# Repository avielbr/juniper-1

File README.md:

### Relevant datasheets:
- [ESP32-S2-WROOM](https://www.4project.co.il/documents/doc_664512_968259.pdf)
- [TMC6200-TA](https://www.mouser.co.il/datasheet/2/256/TMC6200_datasheet_Rev1_05-2529504.pdf) -- I also grabbed what I could from the picture in [this](https://community.simplefoc.com/t/esp32-s3-tmc6200-test-board/2418) thread discussing a board with the same MCU + gate driver.
- [NTMFS5C645NL](https://www.mouser.co.il/datasheet/2/308/NTMFS5C645NL_D-1814050.pdf) MOSFET
- [LDL1117S33R](https://www.mouser.co.il/datasheet/2/389/dm00366442-1799212.pdf) voltage regulator
- [TXU0104PWR](https://www.ti.com/lit/ds/symlink/txu0104.pdf?HQS=dis-mous-null-mousermode-dsf-pf-null-wwe&ts=1665879126738&ref_url=https%253A%252F%252Fwww.mouser.com%252F) level shifter

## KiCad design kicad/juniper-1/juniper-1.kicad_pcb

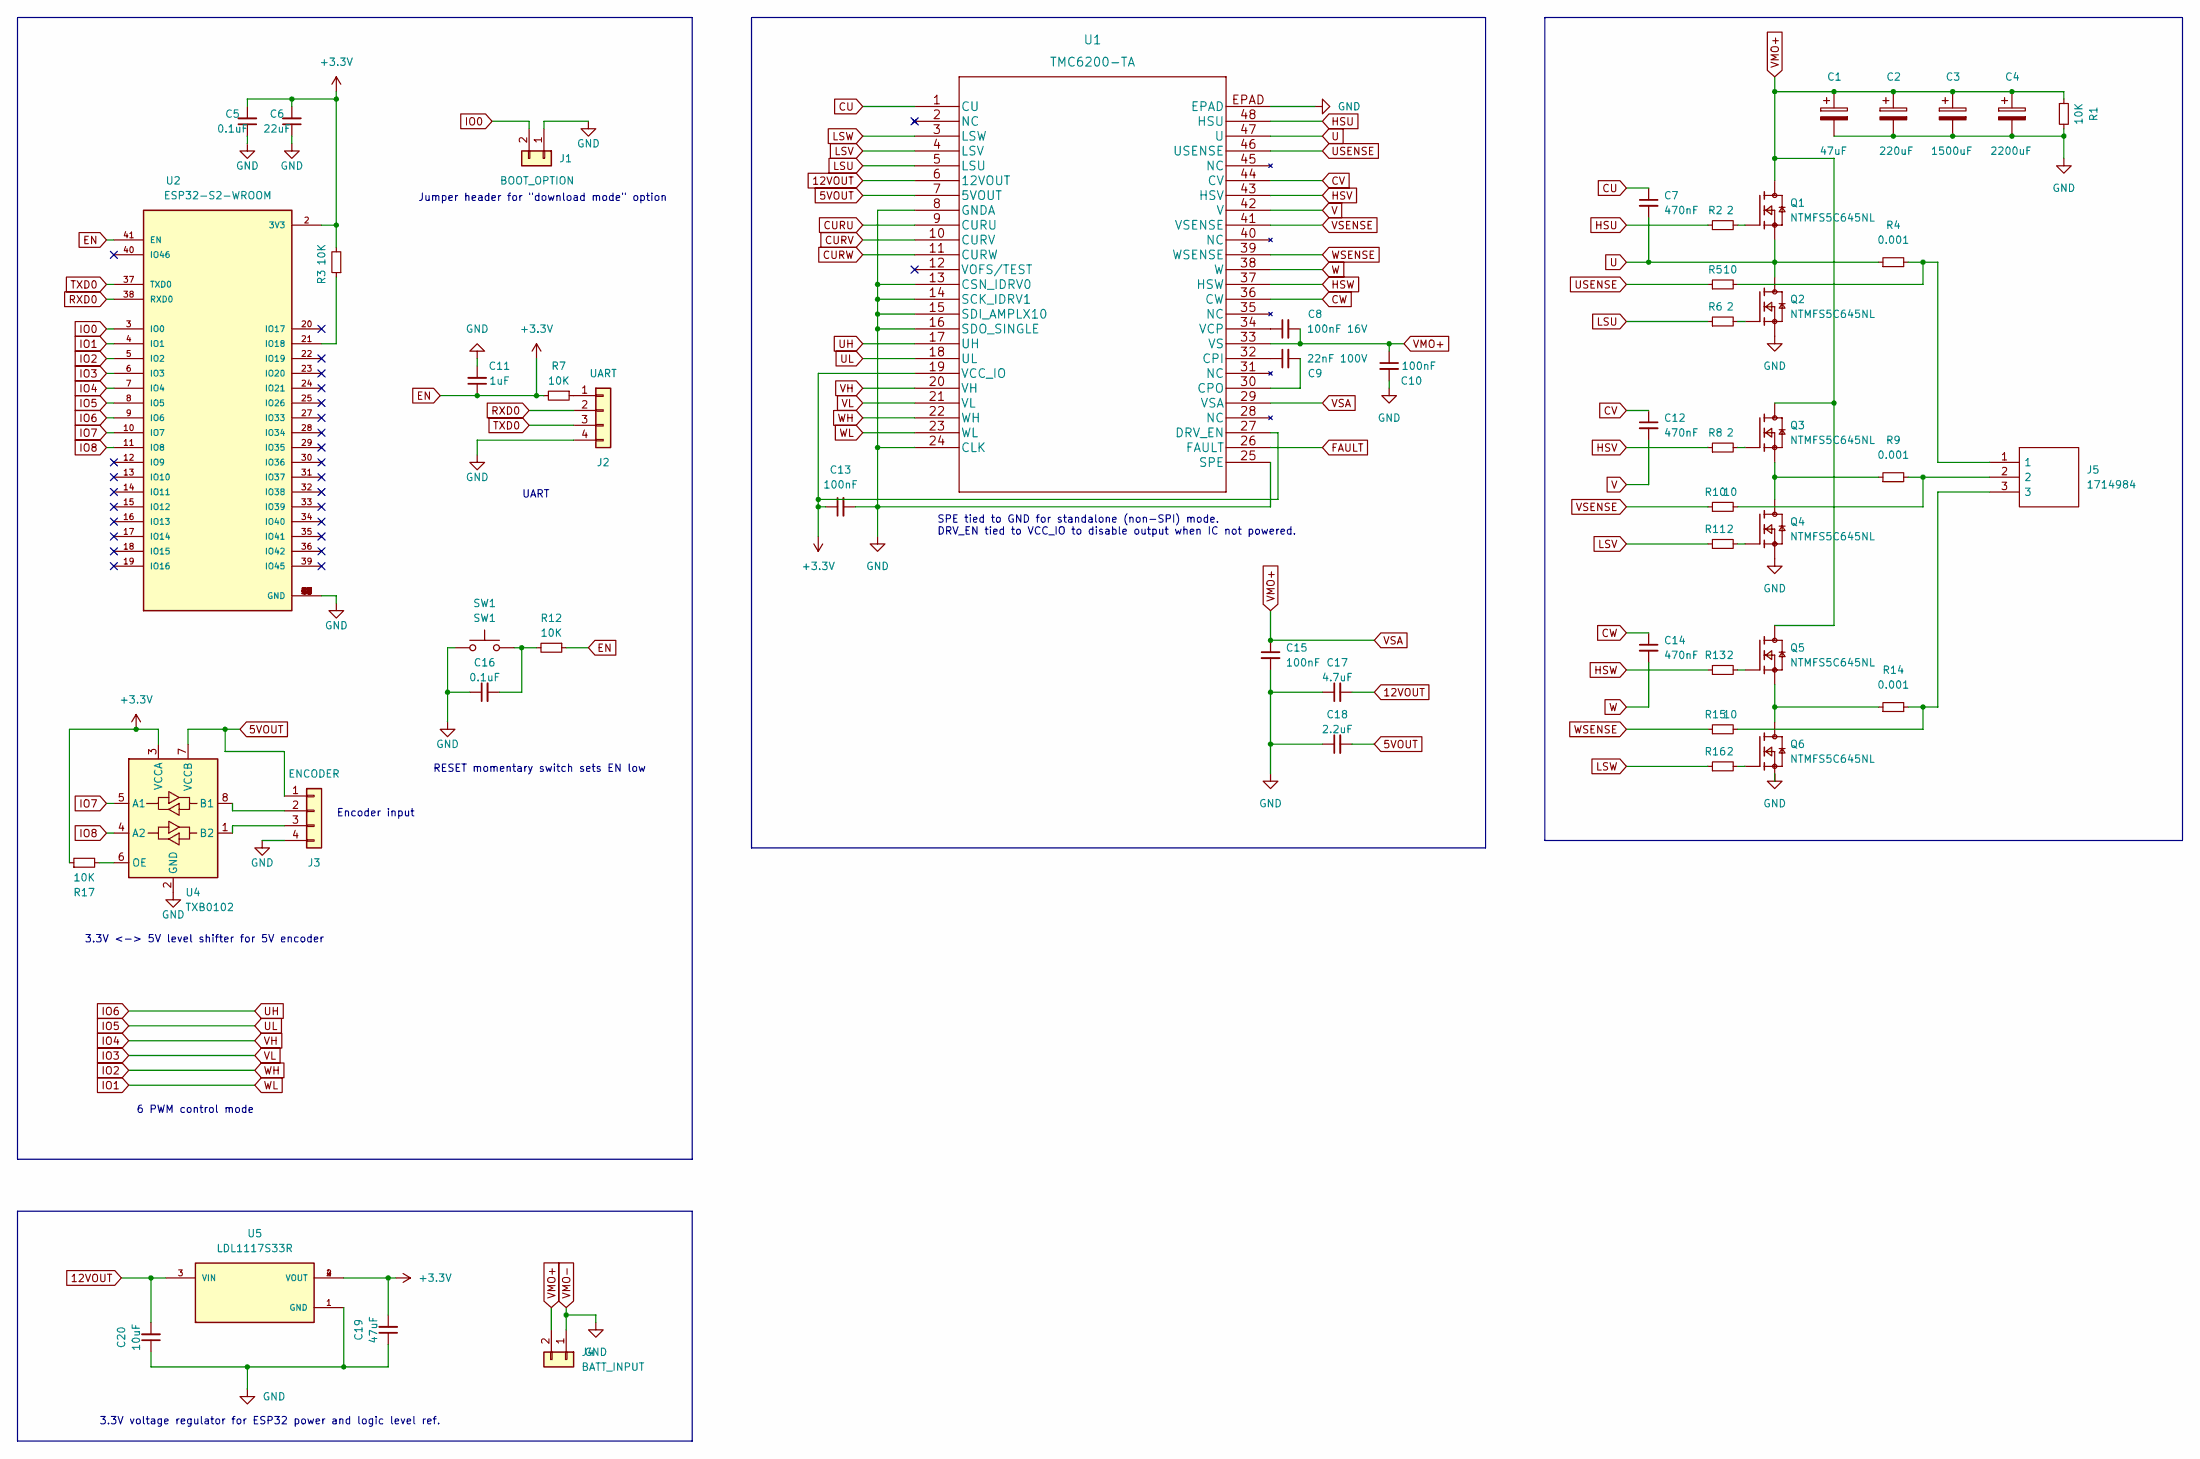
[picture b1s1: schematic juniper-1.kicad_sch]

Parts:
C1: 47uF; CP_Elec_10x10.5
C2: 220uF; CP_Elec_10x10.5
C3: 1500uF; CP_Elec_10x10.5
C4: 2200uF; CP_Elec_10x10.5
C5, C16: 0.1uF; C_0402_1005Metric
C6: 22uF; C_0402_1005Metric
C7, C12, C14: 470nF; C_0402_1005Metric
C8: 100nF 16V; C_0402_1005Metric
C9: 22nF 100V; C_0402_1005Metric
C10, C13, C15: 100nF; C_0402_1005Metric
C11: 1uF; C_0402_1005Metric
C17: 4.7uF; C_0402_1005Metric
C18: 2.2uF; C_0402_1005Metric
C19: 47uF; CP_Elec_6.3x7.7
C20: 10uF; CP_Elec_6.3x7.7
J1: BOOT_OPTION; PinHeader_1x02_P2.54mm_Vertical
J2: UART; PinHeader_1x04_P2.54mm_Vertical
J3: ENCODER; PinSocket_1x04_P2.54mm_Vertical
J4: BATT_INPUT; AMASS_XT60-F_1x02_P7.20mm_Vertical
J5: 1714984; Manufacturer_Part_Number 1714984; Mouser Part Number 651-1714984
Q1, Q2, Q3, Q4, Q5, Q6: NTMFS5C645NL; TRANS_NTMFS5C628NLT1G; PARTREV 1
R1, R3, R7, R12, R17: 10K; R_0603_1608Metric_Pad0.98x0.95mm_HandSolder
R2, R6, R8, R11, R13, R16: 2; R_0603_1608Metric_Pad0.98x0.95mm_HandSolder
R4, R9, R14: 0.001; R_0603_1608Metric_Pad0.98x0.95mm_HandSolder
R5, R10, R15: 10; R_0603_1608Metric_Pad0.98x0.95mm_HandSolder
SW1: SW1; SW_Push_1P1T_NO_CK_PTS125Sx43PSMTR
U1: TMC6200-TA
U2: ESP32-S2-WROOM; XCVR_ESP32-S2-WROOM
U4: TXB0102; TSSOP-8_3x3mm_P0.65mm
U5: LDL1117S33R; SOT230P700X180-4N; PARTREV 7

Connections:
5VOUT: C18.2, J3.1, U1.7 (5VOUT), U4.7 (VCCB)
12VOUT: C17.2, C20.2, U1.6 (12VOUT), U5.3 (VIN)
CU: C7.1, U1.1 (CU)
CURU: U1.9 (CURU)
CURV: U1.10 (CURV)
CURW: U1.11 (CURW)
CV: C12.1, U1.44 (CV)
CW: C14.1, U1.36 (CW)
EN: C5.2, C6.2, C11.1, C13.1, C19.2, R3.2, R7.2, R12.1, R17.1, U1.19 (VCC_IO), U1.27 (DRV_EN), U2.2 (3V3), U2.41 (EN), U4.3 (VCCA), U5.2 (VOUT), U5.4 (VOUT)
FAULT: U1.26 (FAULT)
HSU: R2.1, U1.48 (HSU)
HSV: R8.1, U1.43 (HSV)
HSW: R13.1, U1.37 (HSW)
IO0: J1.2, U2.3 (IO0)
IO1: U1.23 (WL), U2.4 (IO1)
IO2: U1.22 (WH), U2.5 (IO2)
IO3: U1.21 (VL), U2.6 (IO3)
IO4: U1.20 (VH), U2.7 (IO4)
IO5: U1.18 (UL), U2.8 (IO5)
IO6: U1.17 (UH), U2.9 (IO6)
IO7: U2.10 (IO7), U4.5 (A1)
IO8: U2.11 (IO8), U4.4 (A2)
LSU: R6.1, U1.5 (LSU)
LSV: R11.1, U1.4 (LSV)
LSW: R16.1, U1.3 (LSW)
unnamed: C8.1, U1.34 (VCP)
unnamed: C9.1, U1.32 (CPI)
unnamed: C9.2, U1.30 (CPO)
unnamed: C16.2, R12.2, SW1.2
unnamed: J2.1, R7.1
unnamed: J3.2, U4.8 (B1)
unnamed: J3.3, U4.1 (B2)
unnamed: Q1.4, R2.2
unnamed: Q2.4, R6.2
unnamed: Q3.1, Q3.2, Q3.3, Q4.5, R9.1
unnamed: Q3.4, R8.2
unnamed: Q4.4, R11.2
unnamed: Q5.1, Q5.2, Q5.3, Q6.5, R14.1
unnamed: Q5.4, R13.2
unnamed: Q6.4, R16.2
unnamed: J5.1, R4.2, R5.2
unnamed: J5.2, R9.2, R10.2
unnamed: J5.3, R14.2, R15.2
unnamed: R3.1, U2.21 (IO18)
unnamed: R17.2, U4.6 (OE)
RXD0: J2.2, U2.38 (RXD0)
TXD0: J2.3, U2.37 (TXD0)
U: C7.2, Q1.1, Q1.2, Q1.3, Q2.5, R4.1, U1.47 (U)
USENSE: R5.1, U1.46 (USENSE)
V: C12.2, U1.42 (V)
VMO+: C1.1, C2.1, C3.1, C4.1, C8.2, C10.1, C15.1, J4.2, Q1.5, Q3.5, Q5.5, R1.1, U1.29 (VSA), U1.33 (VS)
VMO-: C1.2, C2.2, C3.2, C4.2, C5.1, C6.1, C10.2, C11.2, C13.2, C15.2, C16.1, C17.1, C18.1, C19.1, C20.1, J1.1, J2.4, J3.4, J4.1, Q2.1, Q2.2, Q2.3, Q4.1, Q4.2, Q4.3, Q6.1, Q6.2, Q6.3, R1.2, SW1.1, U1.8 (GNDA), U1.13 (CSN_IDRV0), U1.14 (SCK_IDRV1), U1.15 (SDI_AMPLX10), U1.16 (SDO_SINGLE), U1.24 (CLK), U1.25 (SPE), U1.EPAD, U2.1 (GND), U2.26 (GND), U2.42 (GND), U2.43 (GND), U2.44 (GND), U2.45 (GND), U2.46 (GND), U2.47 (GND), U2.48 (GND), U2.49 (GND), U2.50 (GND), U2.51 (GND), U4.2 (GND), U5.1 (GND)
VSENSE: R10.1, U1.41 (VSENSE)
W: C14.2, U1.38 (W)
WSENSE: R15.1, U1.39 (WSENSE)

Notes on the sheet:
UART
6 PWM control mode
3.3V voltage regulator for ESP32 power and logic level ref.
Jumper header for "download mode" option
RESET momentary switch sets EN low
3.3V <-> 5V level shifter for 5V encoder
SPE tied to GND for standalone (non-SPI) mode. DRV_EN tied to VCC_IO to disable output when IC not powered.
Encoder input

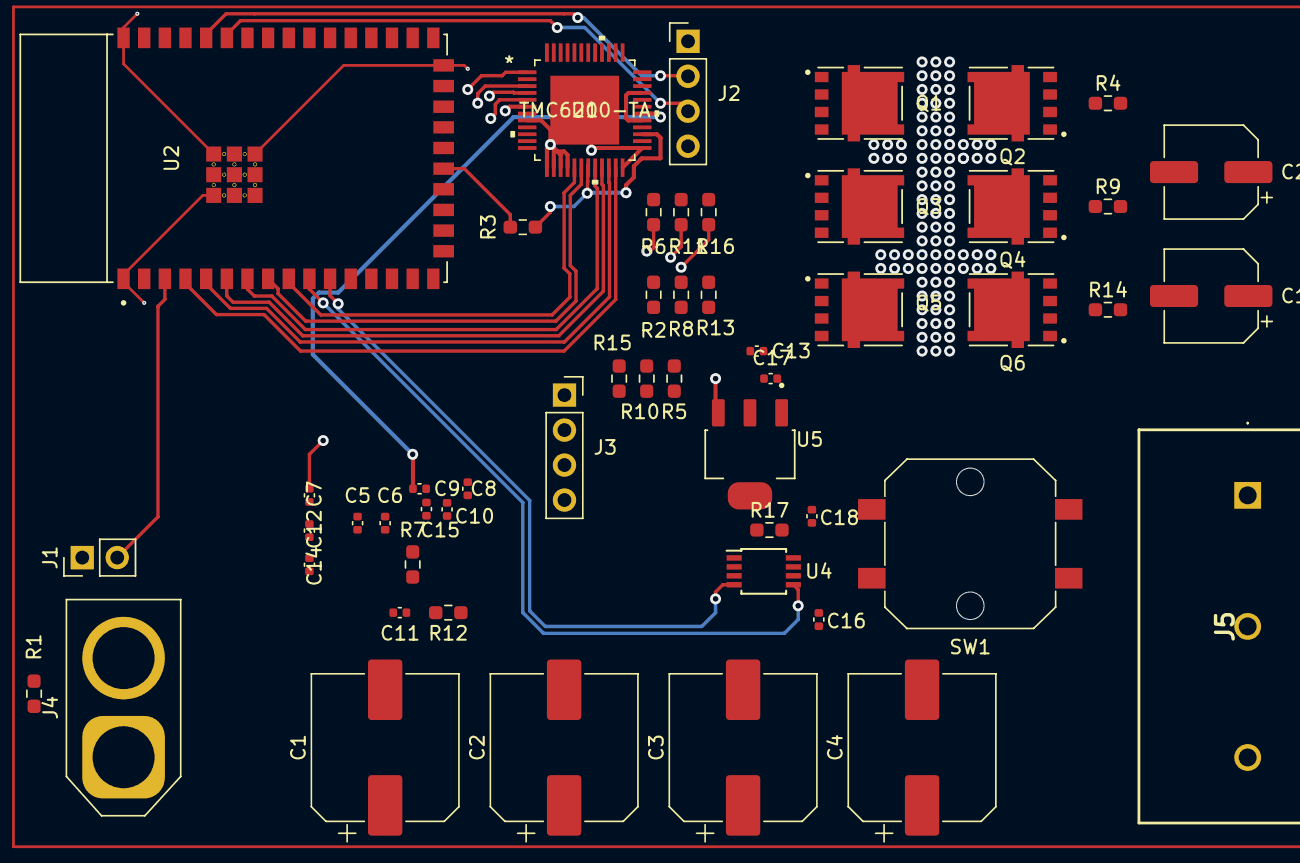
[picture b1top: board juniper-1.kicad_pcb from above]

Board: 4 copper layers, 53 parts (0 on the bottom side), 51 nets.

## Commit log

2022-10-15 Everything before assigning ESP32 pins
2022-10-15 added power supply for ESP32, haven't yet finished assigning esp32 pins
2022-10-15 fixed esp32 symbol, nearly finished assigning pins for MCU
2022-10-16 Fixed voltage regulator, organized, added text, added encoder input
2022-10-16 assigned footprints, just about to start editing board!
2022-10-16 added schematic, started routing
2022-10-17 restarting the pcb layout...
2022-10-17 made lots of progress with rerouting the PCB
2022-10-24 removed current sense for now...

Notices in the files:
parts and their libraries:
Copyright 2021 Accelerated Designs. All rights reserved.
